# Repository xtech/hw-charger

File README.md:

# Universal OpenMower Charger

## Information

This hardware version is in beta state. Expect for things to not work at the current state!

## About This Repo

OpenMower is an open-source project that upgrades off-the-shelf robotic mowers into modern, smart lawn mowing robots with RTK GPS technology. For more details, check out the [OpenMower project](https://github.com/clemensElflein/openmower).

This repository contains the design files for a custom charger specifically designed for converting YardForce mowers to OpenMower. 

## Patents, Local Laws, Liability

Before building a robot based on the designs published here, please make sure that you are allowed to do so in your specific regions.
There may be patents and / or laws prohibiting you of doing so.

The code/schematics/PCB files are distributed in the hope that it will be useful, but WITHOUT ANY WARRANTY; without even the implied warranty of MERCHANTABILITY or FITNESS FOR A PARTICULAR PURPOSE.

This basically means: I'm just documenting a project of mine here for free and I don't have the time and resources to check that devices built using this information will be safe to use, legal to use or even work as intended. You will need technical know-how to use this project and I'm not liable for any damages your devices do to anyone or anything.

## License

<br />This work is licensed under a <a rel="license" href="https://creativecommons.org/licenses/by-nc/4.0/">Creative Commons Attribution-NonCommercial 4.0 International License</a>.

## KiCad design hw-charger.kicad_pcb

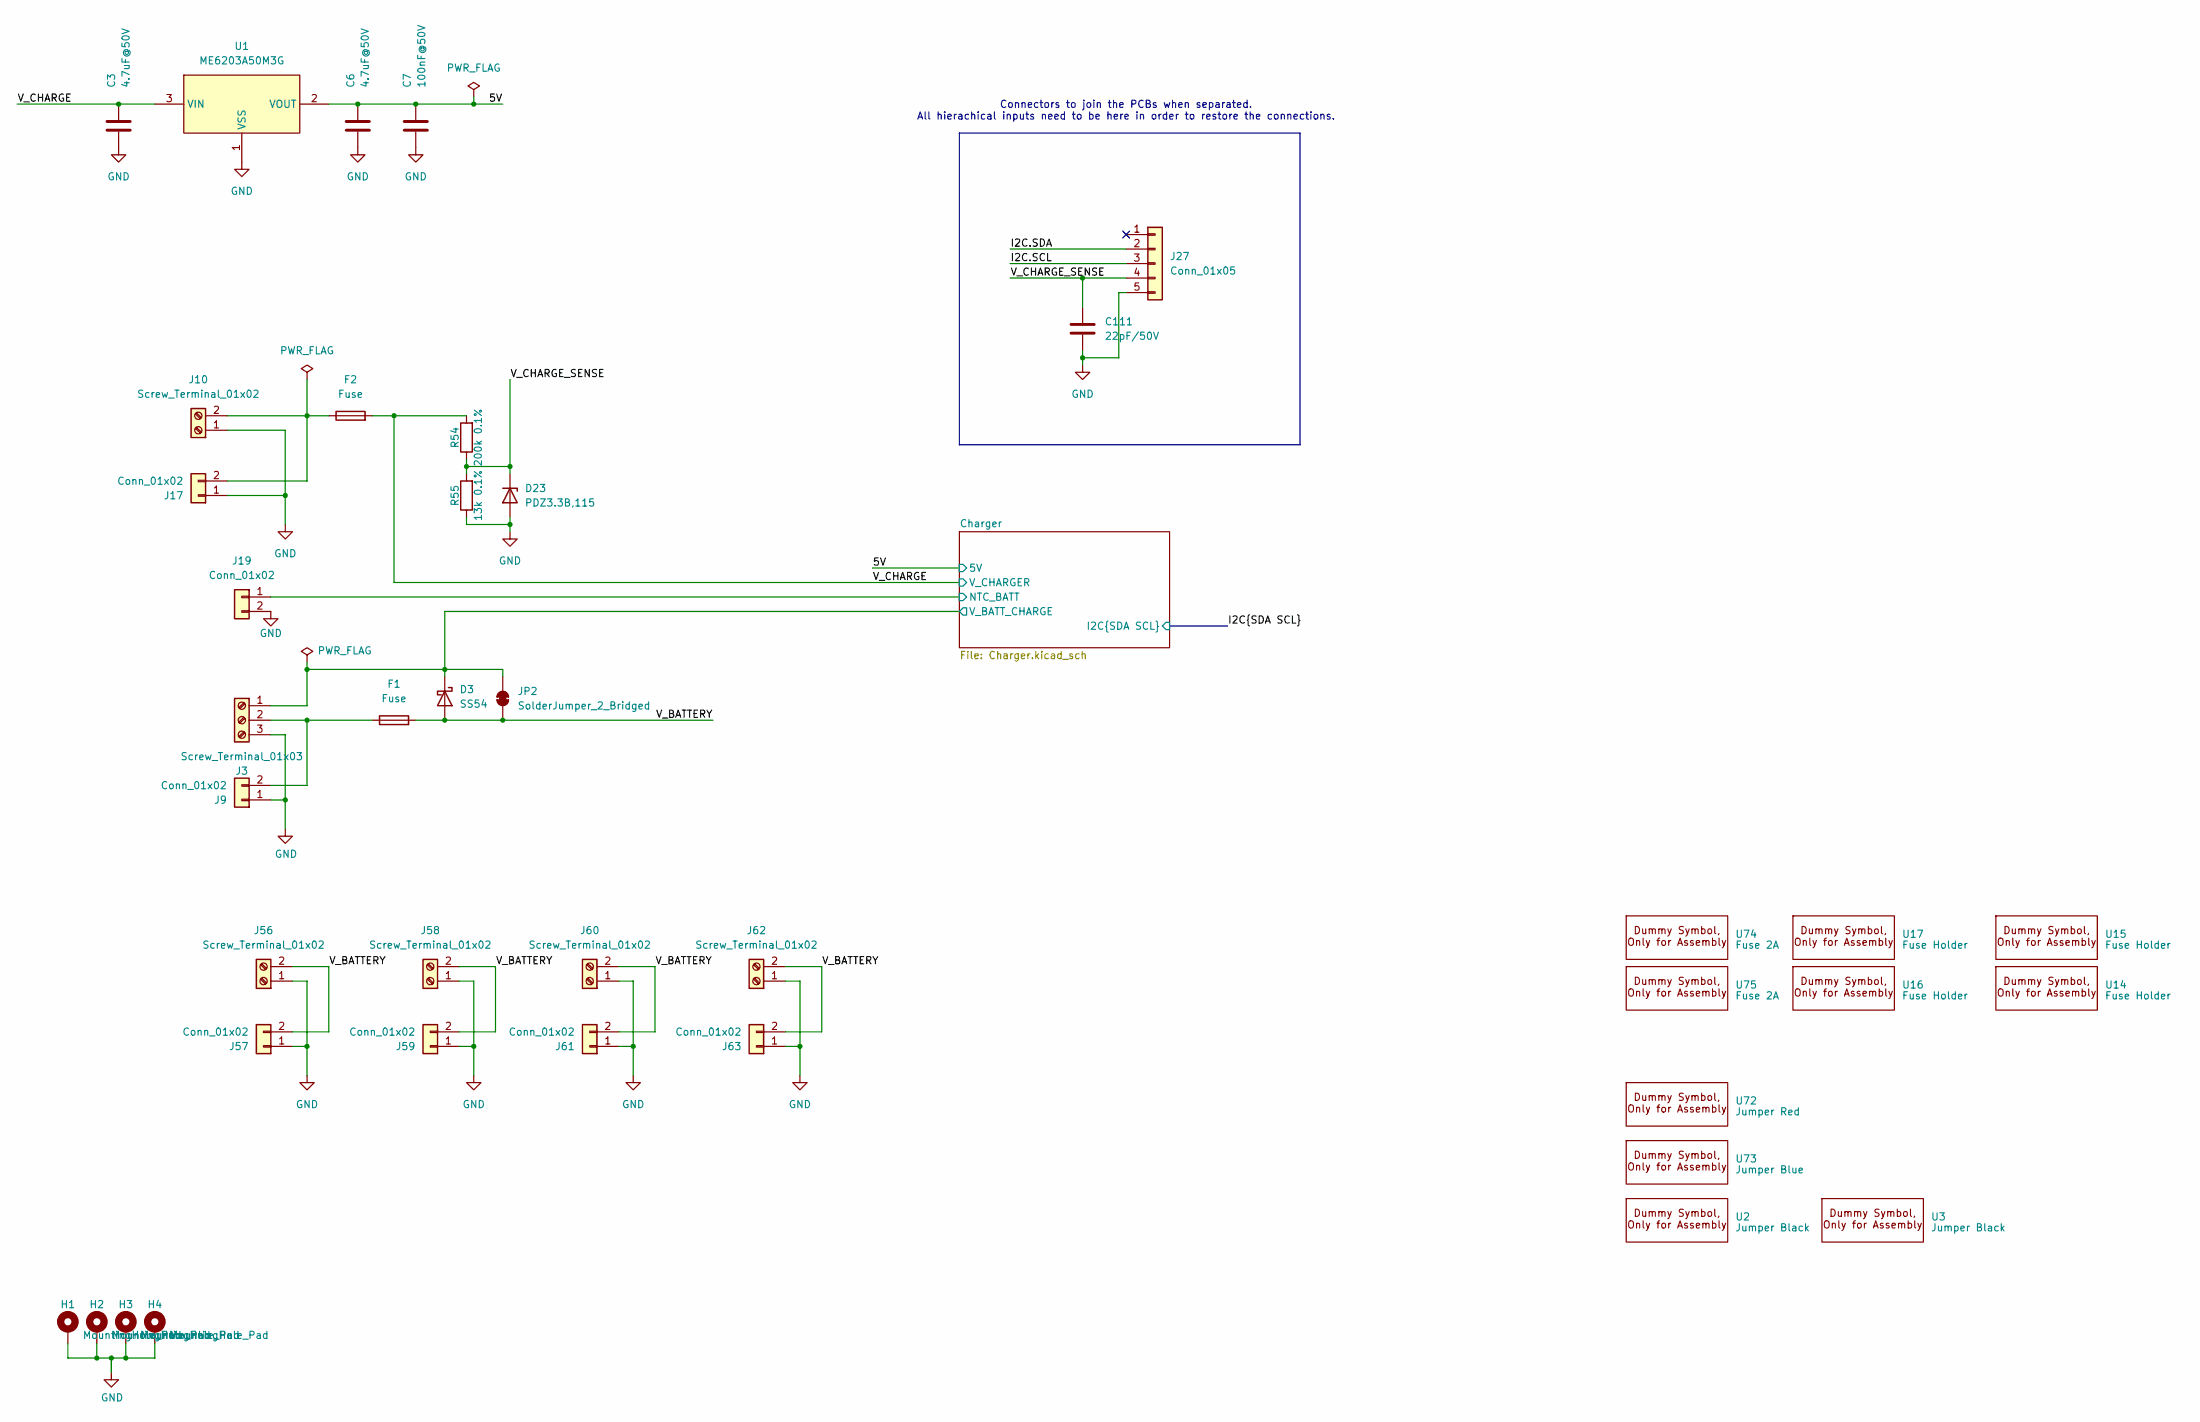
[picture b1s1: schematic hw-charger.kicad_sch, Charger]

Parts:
C3, C6: 4.7uF@50V; C_1206_3216Metric; JLC C29823
C7: 100nF@50V; C_0603_1608Metric; JLC C14663
C111: 22pF/50V; C_0603_1608Metric; JLC C1653
D3: SS54; D_SMA; Part Number SB54AFC_R1_00001; Digikey 3757-SB54AFC_R1_00001CT-ND
D23: PDZ3.3B,115; D_SOD-323; JLC C426855
F1, F2: Fuse; Fuseholder5x20_horiz_open_inline_C3130; JLC C3130
H1, H2, H3, H4: MountingHole_Pad; MountingHole_4.3mm_M4_Pad_Via
J3: Screw_Terminal_01x03; TerminalBlock_Phoenix_MKDS-1,5-3-5.08_1x03_P5.08mm_Horizont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; JLC C557666
J9, J17: Conn_01x02; AMASS_XT30U-M_1x02_P5.0mm_Vertical_mod; JLC C99101
J10, J56, J58, J60, J62: Screw_Terminal_01x02; TerminalBlock_Phoenix_MKDS-1,5-2-5.08_1x02_P5.08mm_Horizont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; JLC C557665
J19: Conn_01x02; JST_XH_B2B-XH-A_1x02_P2.50mm_Vertical; JLC C2910525
J27: Conn_01x05; JST_XH_B5B-XH-A_1x05_P2.50mm_Vertical; JLC C157991
J57, J59, J61, J63: Conn_01x02; AMASS_XT30U-F_1x02_P5.0mm_Vertical_mod; JLC C99102
JP2: SolderJumper_2_Bridged; SolderJumper-2_P1.3mm_Bridged2Bar_Pad1.0x1.5mm
R54: 200k 0.1%; R_0402_1005Metric; JLC C728556
R55: 13k 0.1%; R_0402_1005Metric; JLC C852524
U1: ME6203A50M3G; SOT-23-3_L2.9-W1.6-P1.90-LS2.8-BR; LCSC Part C92717
U2, U3: Jumper Black; SNT-100-BK-H; JLC C100114
U14, U15, U16, U17: Fuse Holder; Dummy; JLC C3130
U72: Jumper Red; SNT-100-RD-G; JLC C20417889
U73: Jumper Blue; SNT-100-BL-H; JLC C20417886
U74, U75: Fuse 2A; Dummy; JLC C356459

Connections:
/5V: C6.1, C7.2, U1.2 (VOUT); also elsewhere on the board
/Charger/NTC_BATT: J19.1; also elsewhere on the board
/Charger/V_BATT_CHARGE: D3.1 (K), J3.1, JP2.2 (B); also elsewhere on the board
/I2C.SCL: J27.3; also elsewhere on the board
/I2C.SDA: J27.2; also elsewhere on the board
/V_BATTERY: D3.2 (A), F1.2, J56.2, J57.2, J58.2, J59.2, J60.2, J61.2, J62.2, J63.2, JP2.1 (A)
/V_CHARGE: C3.1, F2.2, R54.2, U1.3 (VIN); also elsewhere on the board
/V_CHARGE_SENSE: C111.1, D23.1 (K), J27.4, R54.1, R55.2
GND: C3.2, C6.2, C7.1, C111.2, D23.2 (A), H1.1, H2.1, H3.1, H4.1, J3.3, J9.1, J10.1, J17.1, J19.2, J27.5, J56.1, J57.1, J58.1, J59.1, J60.1, J61.1, J62.1, J63.1, R55.1, U1.1 (VSS); also elsewhere on the board
unnamed: F1.1, J3.2, J9.2
unnamed: F2.1, J10.2, J17.2

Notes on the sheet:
Connectors to join the PCBs when separated. All hierachical inputs need to be here in order to restore the connections.

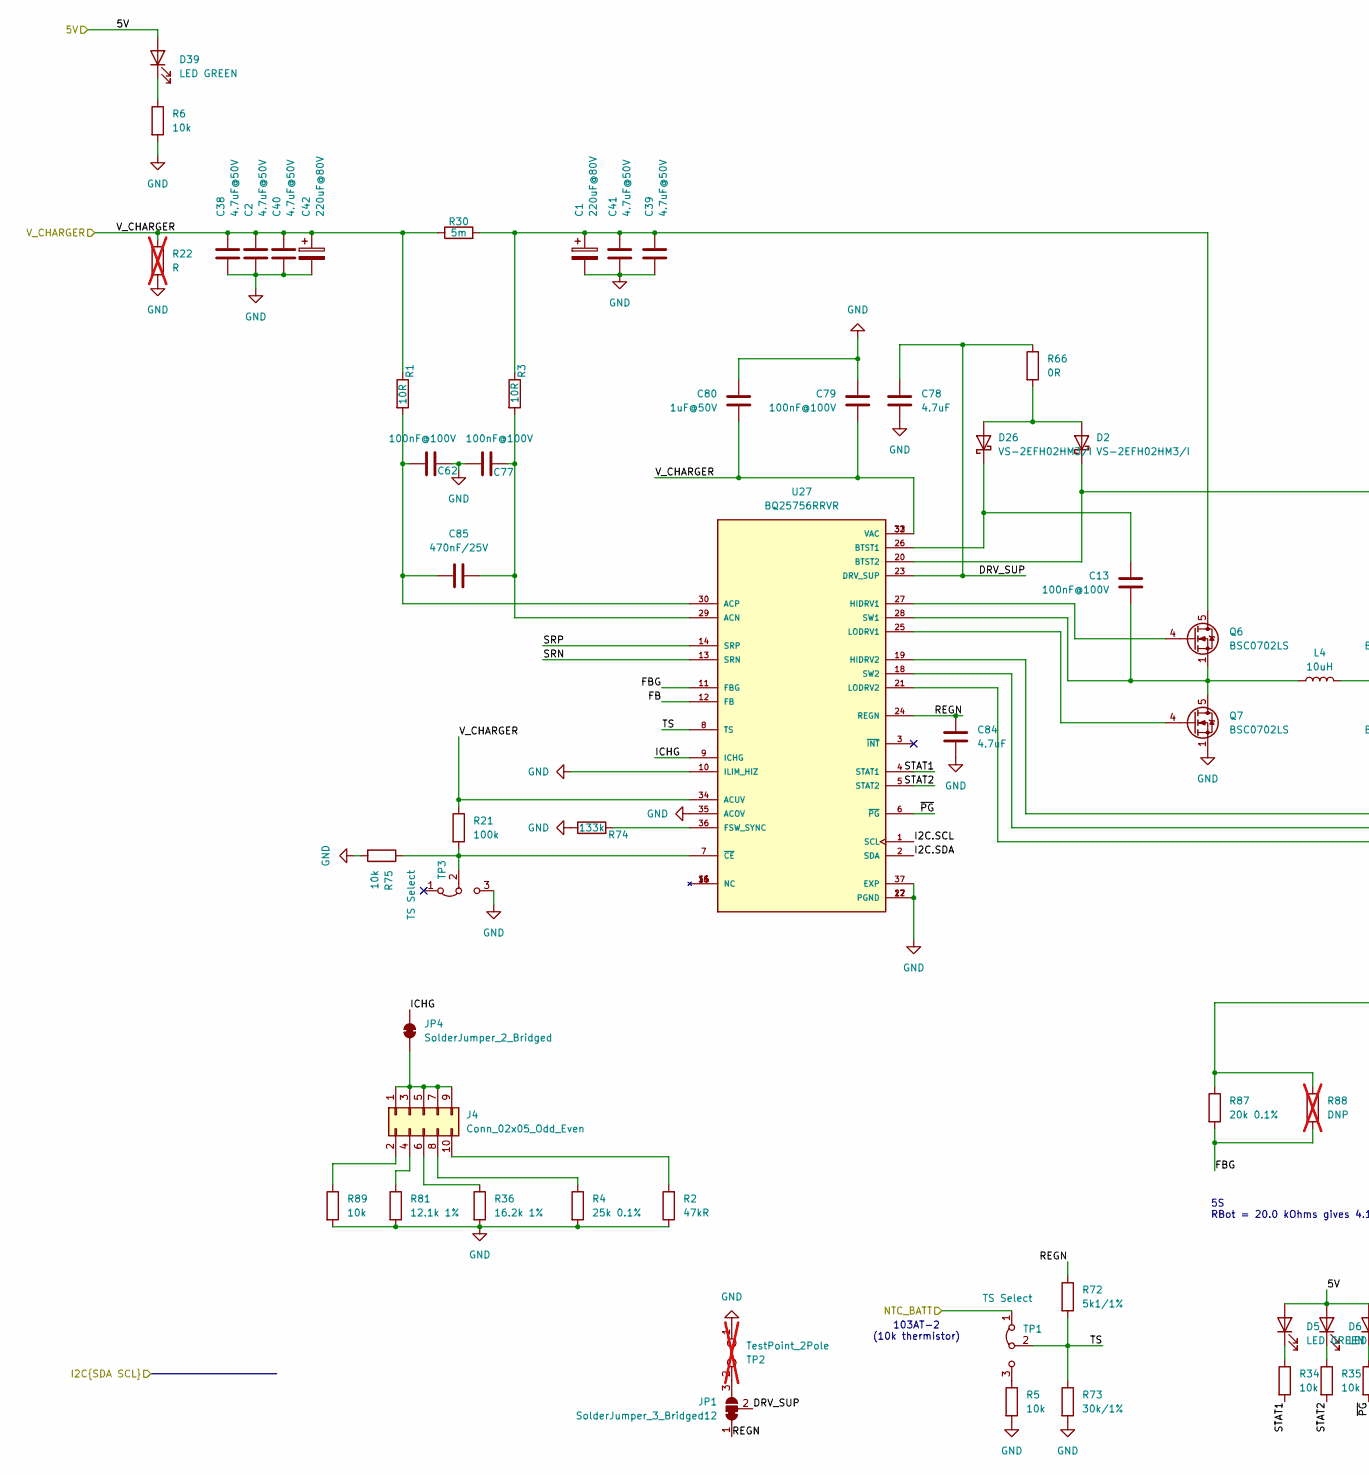
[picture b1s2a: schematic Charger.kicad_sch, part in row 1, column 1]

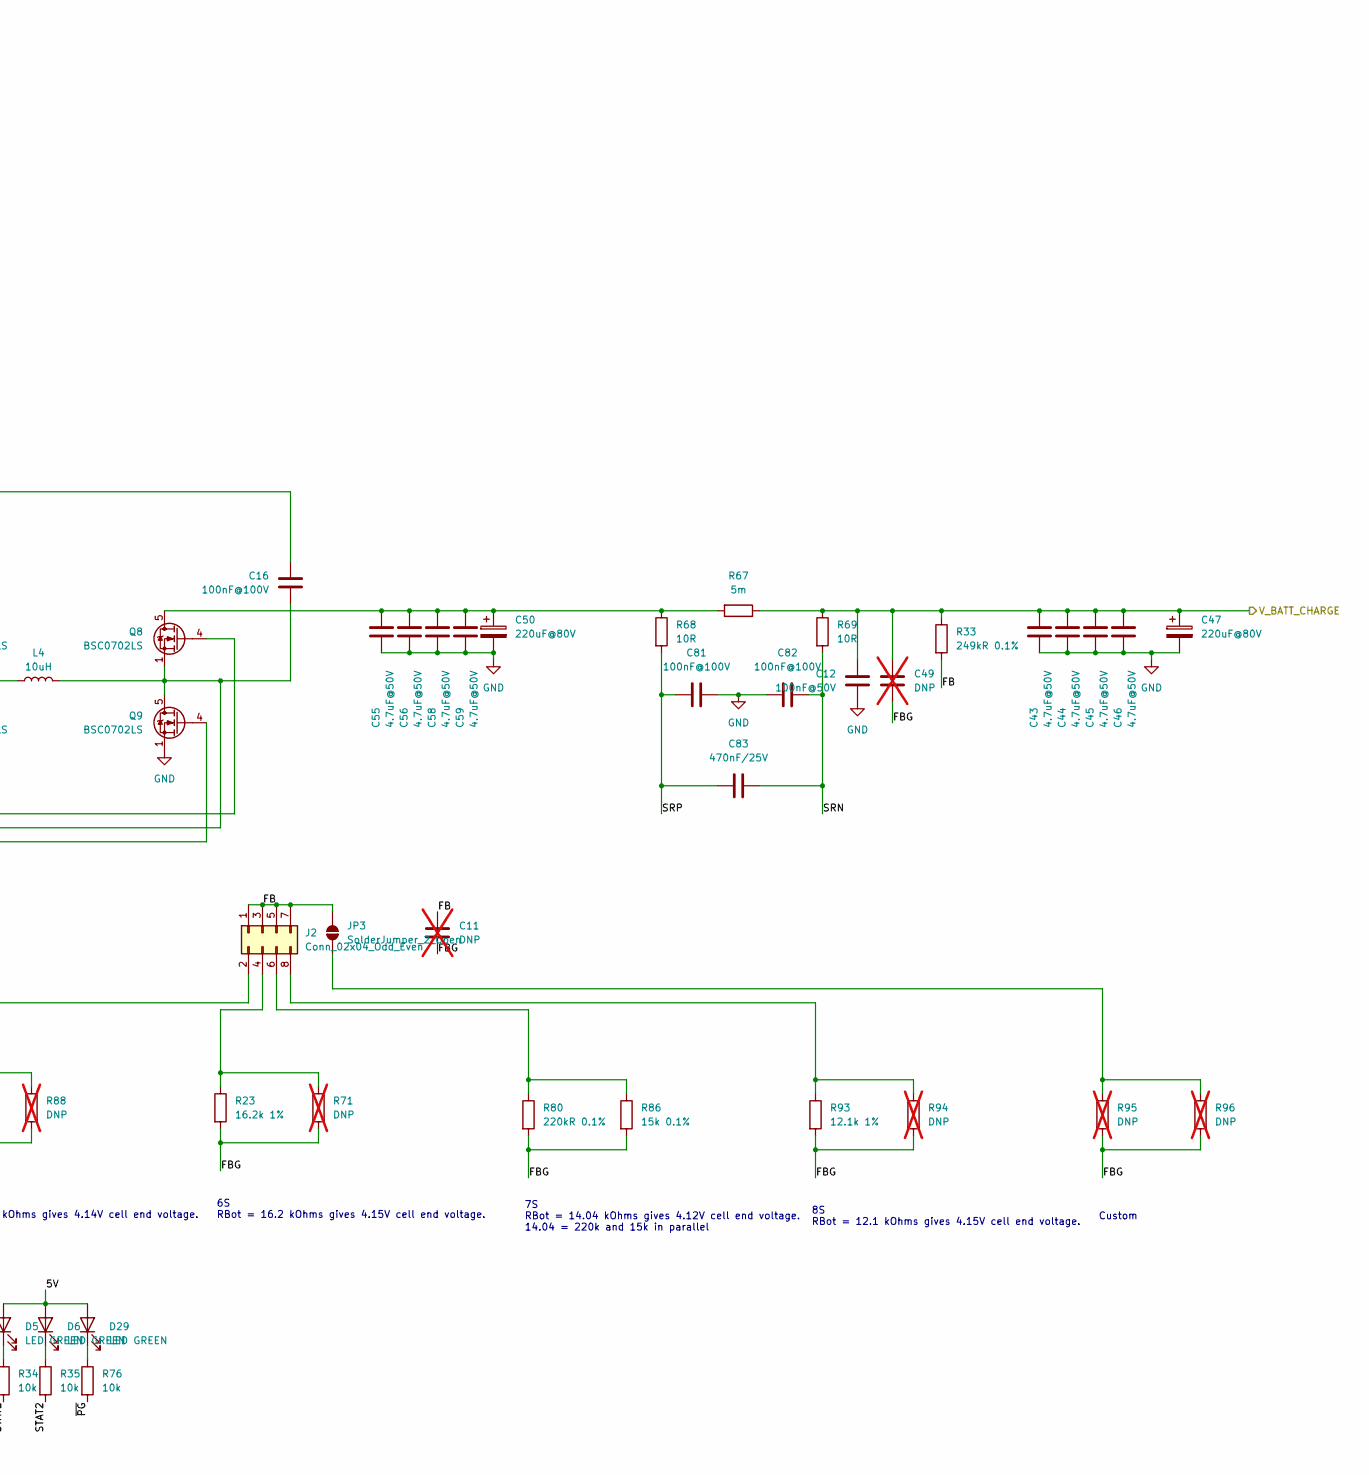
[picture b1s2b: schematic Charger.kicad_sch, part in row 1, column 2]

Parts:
C1, C42, C47, C50: 220uF@80V; CP_Radial_D10.0mm_P5.00mm; JLC C2937593
C2, C38, C39, C40, C41, C43, C44, C45, C46, C55, C56, C58, C59: 4.7uF@50V; C_1206_3216Metric; JLC C29823
C11, C49: DNP; C_0603_1608Metric; not fitted
C12: 100nF@50V; C_0603_1608Metric; JLC C14663
C13, C16, C62, C77, C79, C81, C82: 100nF@100V; C_0805_2012Metric; JLC C28233
C78, C84: 4.7uF; C_0805_2012Metric; JLC C1779
C80: 1uF@50V; C_0805_2012Metric; JLC C28323
C83, C85: 470nF/25V; C_0603_1608Metric; JLC C1623
D2, D26: VS-2EFH02HM3/I; D_SMF; JLC C241868
D5, D6, D29, D39: LED GREEN; LED_0805_2012Metric; JLC C2297
J2: Conn_02x04_Odd_Even; PinHeader_2x04_P2.54mm_Vertical; JLC C5383105
J4: Conn_02x05_Odd_Even; PinHeader_2x05_P2.54mm_Vertical; JLC C706895
JP1: SolderJumper_3_Bridged12; SolderJumper-3_P1.3mm_Bridged12_Pad1.0x1.5mm
JP3: SolderJumper_2_Open; SolderJumper-2_P1.3mm_Open_Pad1.0x1.5mm
JP4: SolderJumper_2_Bridged; SolderJumper-2_P1.3mm_Bridged_Pad1.0x1.5mm
L4: 10uH; L_Sunlord_MWSA1004S; JLC C408487
Q6, Q7, Q8, Q9: BSC0702LS; TDSON-8-1; JLC C501503
R1, R3, R68, R69: 10R; R_0603_1608Metric; JLC C22859
R2: 47kR; R_0603_1608Metric; JLC C25819
R4: 25k 0.1%; R_0603_1608Metric; JLC C2828637
R5, R6, R34, R35, R75, R76: 10k; R_0402_1005Metric; JLC C25744
R21: 100k; R_0402_1005Metric; JLC C25741
R22: R; R_1206_3216Metric; not fitted
R23, R36: 16.2k 1%; R_0603_1608Metric; JLC C22885
R30, R67: 5m; R_2512_6332Metric; JLC C185817
R33: 249kR 0.1%; R_0603_1608Metric; JLC C705752
R66: 0R; R_0805_2012Metric; JLC C17477
R71, R88, R94, R95, R96: DNP; R_0603_1608Metric; not fitted
R72: 5k1/1%; R_0603_1608Metric; JLC C23186
R73: 30k/1%; R_0603_1608Metric; JLC C22984
R74: 133k; R_0603_1608Metric; JLC C227577
R80: 220kR 0.1%; R_0603_1608Metric; JLC C278545
R81, R93: 12.1k 1%; R_0603_1608Metric; JLC C22864
R86: 15k 0.1%; R_0603_1608Metric; JLC C2692707
R87: 20k 0.1%; R_0603_1608Metric; JLC C4184
R89: 10k; R_0603_1608Metric; JLC C25804
TP1, TP3: TS Select; PinHeader_1x03_P2.54mm_Vertical; JLC C49257
TP2: TestPoint_2Pole; PinHeader_1x02_P2.54mm_Vertical; not fitted
U27: BQ25756RRVR; PARTREV August 2023; JLC C19272232

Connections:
/5V: D5.2 (A), D6.2 (A), D29.2 (A), D39.2 (A); also elsewhere on the board
/Charger/DRV_SUP: C78.1, JP1.2 (C), R66.1, U27.23 (DRV_SUP)
/Charger/FB: C11.1, J2.1, J2.3, J2.5, J2.7, JP3.2 (B), R33.2, U27.12 (FB)
/Charger/FBG: C11.2, C49.2, R23.2, R71.2, R80.2, R86.2, R87.2, R88.2, R93.2, R94.2, R95.2, R96.2, U27.11 (FBG)
/Charger/ICHG: JP4.2 (B), U27.9 (ICHG)
/Charger/NTC_BATT: TP1.1 (A); also elsewhere on the board
/Charger/REGN: C84.1, JP1.1 (A), R72.1, U27.24 (REGN)
/Charger/SRN: C82.1, C83.2, R69.2, U27.13 (SRN)
/Charger/SRP: C81.2, C83.1, R68.2, U27.14 (SRP)
/Charger/STAT1: R34.2, U27.4 (STAT1)
/Charger/STAT2: R35.2, U27.5 (STAT2)
/Charger/TS: R72.2, R73.1, TP1.2 (C), U27.8 (TS)
/Charger/V_BATT_CHARGE: C12.2, C43.1, C44.1, C45.1, C46.1, C47.1, C49.1, R33.1, R67.1, R69.1; also elsewhere on the board
/Charger/~PG: R76.2, U27.6 (~PG)
/I2C.SCL: U27.1 (SCL); also elsewhere on the board
/I2C.SDA: U27.2 (SDA); also elsewhere on the board
/V_CHARGE: C2.1, C38.1, C40.1, C42.1, C79.1, C80.1, R1.1, R21.1, R22.1, R30.1, U27.32 (VAC), U27.33 (VAC), U27.34 (ACUV); also elsewhere on the board
GND: C1.2, C2.2, C12.1, C38.2, C39.2, C40.2, C41.2, C42.2, C43.2, C44.2, C45.2, C46.2, C47.2, C50.2, C55.2, C56.2, C58.2, C59.2, C62.2, C77.1, C78.2, C79.2, C80.2, C81.1, C82.2, C84.2, Q7.1 (S), Q7.2 (S), Q7.3 (S), Q9.1 (S), Q9.2 (S), Q9.3 (S), R2.1, R4.2, R5.2, R6.2, R22.2, R36.2, R73.2, R74.1, R75.2, R81.2, R89.2, TP2.1, TP3.3 (B), U27.10 (ILIM_HIZ), U27.17 (PGND), U27.22 (PGND), U27.35 (ACOV), U27.37 (EXP); also elsewhere on the board
unnamed: D2.2 (A), D26.2 (A), R66.2
unnamed: C16.2, D2.1 (K), U27.20 (BTST2)
unnamed: D5.1 (K), R34.1
unnamed: D6.1 (K), R35.1
unnamed: C13.2, D26.1 (K), U27.26 (BTST1)
unnamed: D29.1 (K), R76.1
unnamed: D39.1 (K), R6.1
unnamed: J2.2, R87.1, R88.1
unnamed: J2.4, R23.1, R71.1
unnamed: J2.6, R80.1, R86.1
unnamed: J2.8, R93.1, R94.1
unnamed: J4.1, J4.3, J4.5, J4.7, J4.9, JP4.1 (A)
unnamed: J4.2, R89.1
unnamed: J4.4, R81.1
unnamed: J4.6, R36.1
unnamed: J4.8, R4.1
unnamed: J4.10, R2.2
unnamed: JP1.3 (B), TP2.2
unnamed: JP3.1 (A), R95.1, R96.1
unnamed: C1.1, C39.1, C41.1, Q6.5 (D), R3.1, R30.2
unnamed: Q6.4 (G), U27.27 (HIDRV1)
unnamed: C13.1, L4.1, Q6.1 (S), Q6.2 (S), Q6.3 (S), Q7.5 (D), U27.28 (SW1)
unnamed: Q7.4 (G), U27.25 (LODRV1)
unnamed: C50.1, C55.1, C56.1, C58.1, C59.1, Q8.5 (D), R67.2, R68.1
unnamed: Q8.4 (G), U27.19 (HIDRV2)
unnamed: C16.1, L4.2, Q8.1 (S), Q8.2 (S), Q8.3 (S), Q9.5 (D), U27.18 (SW2)
unnamed: Q9.4 (G), U27.21 (LODRV2)
unnamed: R5.1, TP1.3 (B)
unnamed: R21.2, R75.1, TP3.2 (C), U27.7 (~CE)
unnamed: C77.2, C85.1, R3.2, U27.29 (ACN)
unnamed: C62.1, C85.2, R1.2, U27.30 (ACP)
unnamed: R74.2, U27.36 (FSW_SYNC)

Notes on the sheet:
6S RBot = 16.2 kOhms gives 4.15V cell end voltage.
103AT-2 (10k thermistor)
Custom
7S RBot = 14.04 kOhms gives 4.12V cell end voltage. 14.04 = 220k and 15k in parallel
5S RBot = 20.0 kOhms gives 4.14V cell end voltage.
8S RBot = 12.1 kOhms gives 4.15V cell end voltage.

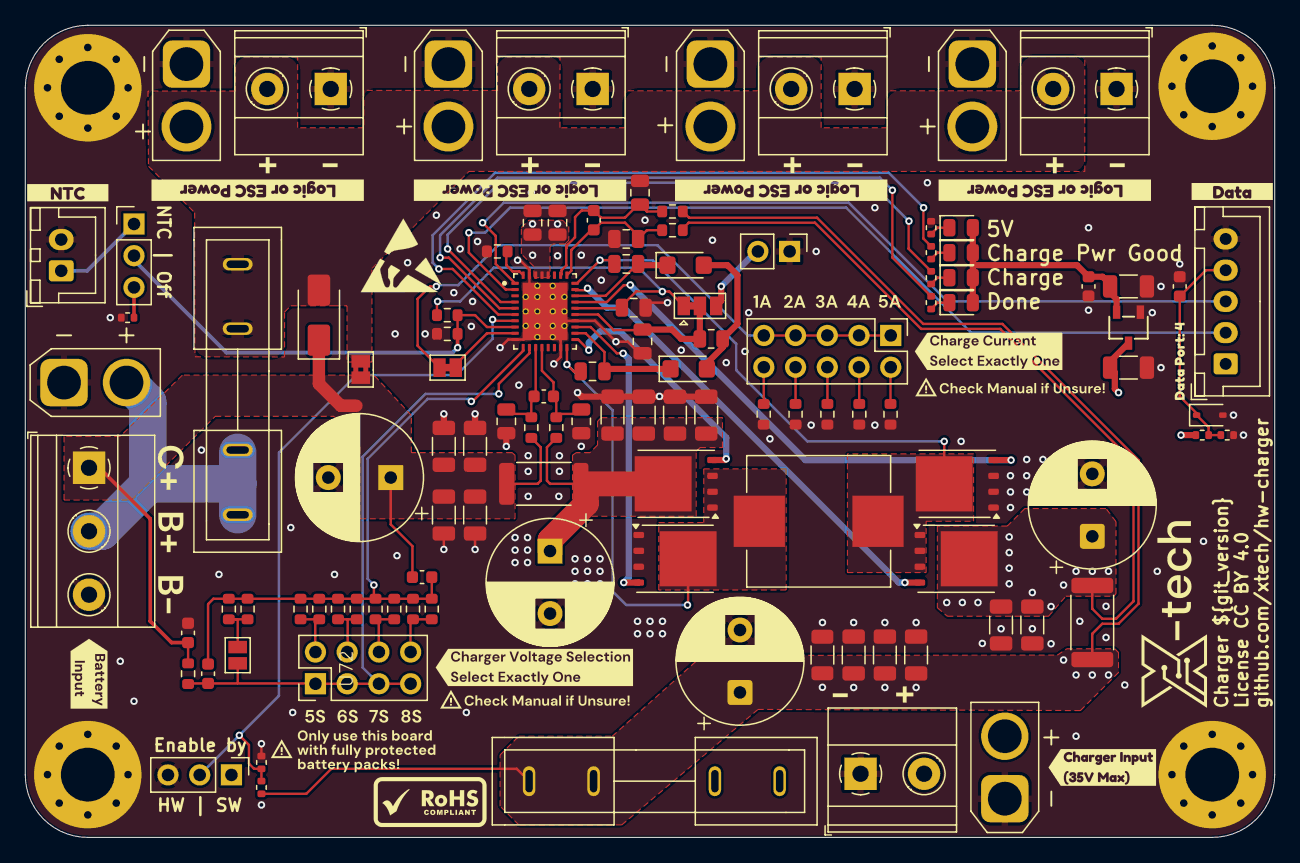
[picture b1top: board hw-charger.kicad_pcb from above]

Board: 4 copper layers, 100.0 x 65.0 mm, 163 parts (0 on the bottom side), 54 nets.

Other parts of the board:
LOGO2: ESD-Logo_6.6x6mm_SilkScreen
kibuzzard-69C99438, kibuzzard-69C99438#2, kibuzzard-69C99438#3: G***; kibuzzard-69C99438
kibuzzard-69C99648: G***; kibuzzard-69C99648
kibuzzard-69CD6E52: G***; kibuzzard-69CD6E52
kibuzzard-69CEE1A3: G***; kibuzzard-69CEE1A3
kibuzzard-69CEE455: G***; kibuzzard-69CEE455
kibuzzard-69CEEB52: G***; kibuzzard-69CEEB52
kibuzzard-69CFD05E: G***; kibuzzard-69CFD05E
kibuzzard-69CFD081: G***; kibuzzard-69CFD081
kibuzzard-670E8F90: G***; kibuzzard-670E8F90
kibuzzard-670E90ED, kibuzzard-670E90ED#2: G***; kibuzzard-670E90ED
kibuzzard-670E91C7: G***; kibuzzard-670E91C7
kibuzzard-670E91D3: G***; kibuzzard-670E91D3
kibuzzard-670E91D8: G***; kibuzzard-670E91D8
kibuzzard-670E91E3: G***; kibuzzard-670E91E3
kibuzzard-6711AB8A: G***; kibuzzard-6711AB8A
kibuzzard-68532E1B, kibuzzard-68532E1B#2, kibuzzard-68532E1B#3, kibuzzard-68532E1B#4, kibuzzard-68532E1B#5: G***; kibuzzard-68532E1B
kibuzzard-68532E12, kibuzzard-68532E12#2, kibuzzard-68532E12#3, kibuzzard-68532E12#4, kibuzzard-68532E12#5: G***; kibuzzard-68532E12
kibuzzard-671188B5: G***; kibuzzard-671188B5
kibuzzard-671188C2: G***; kibuzzard-671188C2
kibuzzard-671188D3: G***; kibuzzard-671188D3
kibuzzard-671188DE: G***; kibuzzard-671188DE
kibuzzard-671188EA: G***; kibuzzard-671188EA
kibuzzard-67111882: G***; kibuzzard-67111882
kibuzzard-67111937: G***; kibuzzard-67111937
kibuzzard-67111945: G***; kibuzzard-67111945

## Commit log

2026-03-31 Init
2026-03-31 Add step 3D rendering
2026-03-31 Revert "Add step 3D rendering"
    This reverts commit bc3f8788ed7dc011e9aa616567f74195ffffa81b.
2026-03-31 Add FT rotations and kibot filter and set fuses DNP
2026-04-01 Add AC-Sense
2026-04-03 Add /CE, NTC Selector, 5V LDO. Fix copper traces, vias in pads and this and that
2026-04-03 Fixed CE pin connection; Use git version as variable
2026-04-03 deploy: cd6257762f24f67b626567c4692f5e4b6c721154

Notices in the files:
Charger.kicad_sch:
License CC BY 4.0
